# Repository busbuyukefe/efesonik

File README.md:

# efesonik (v2)

A directional soundbar proof-of-concept using cheap 40kHz transducers.

This project can work with the code from [gururise](https://github.com/gururise/directional_speaker) and uses the STM32-bluepill library of [yet-another-average-joe](https://github.com/yet-another-average-joe/Kicad-STM32)

On the [PDF](https://github.com/busbuyukefe/efesonik/blob/main/Parametrik%20Hoparl%C3%B6r.pdf) you can find my notes about the price, working principle and things like layout of the transducers I took while planning/designing the project.

This system has a set of parametric-speaker arranged side-by-side with independent angle control for each one. This allows the system to be focused on more than one targets thus making a more usable. With each section being able to rotate independently it takes less space with the rotating-mechanism than a single speaker with a gimbal.

You can see the code I used in this [gist](https://gist.github.com/busbuyukefe/7ff0d10a8e1e2d5ed5e22a36067409bf) I posted quite a while ago (Which is essentialy the same code from gururise but with a different pinout)

In the amp section of the block diagram you can use anything else to handle the switching. 
The KiCAD drawing has a single sided PCB design but I didn't had the time to check if it is working.

## I sold this project to someone around March of 2021 so I no longer have it.

Video of the first test with the STM32 driver using an old parametric array I built:

Some photos I took during building it:

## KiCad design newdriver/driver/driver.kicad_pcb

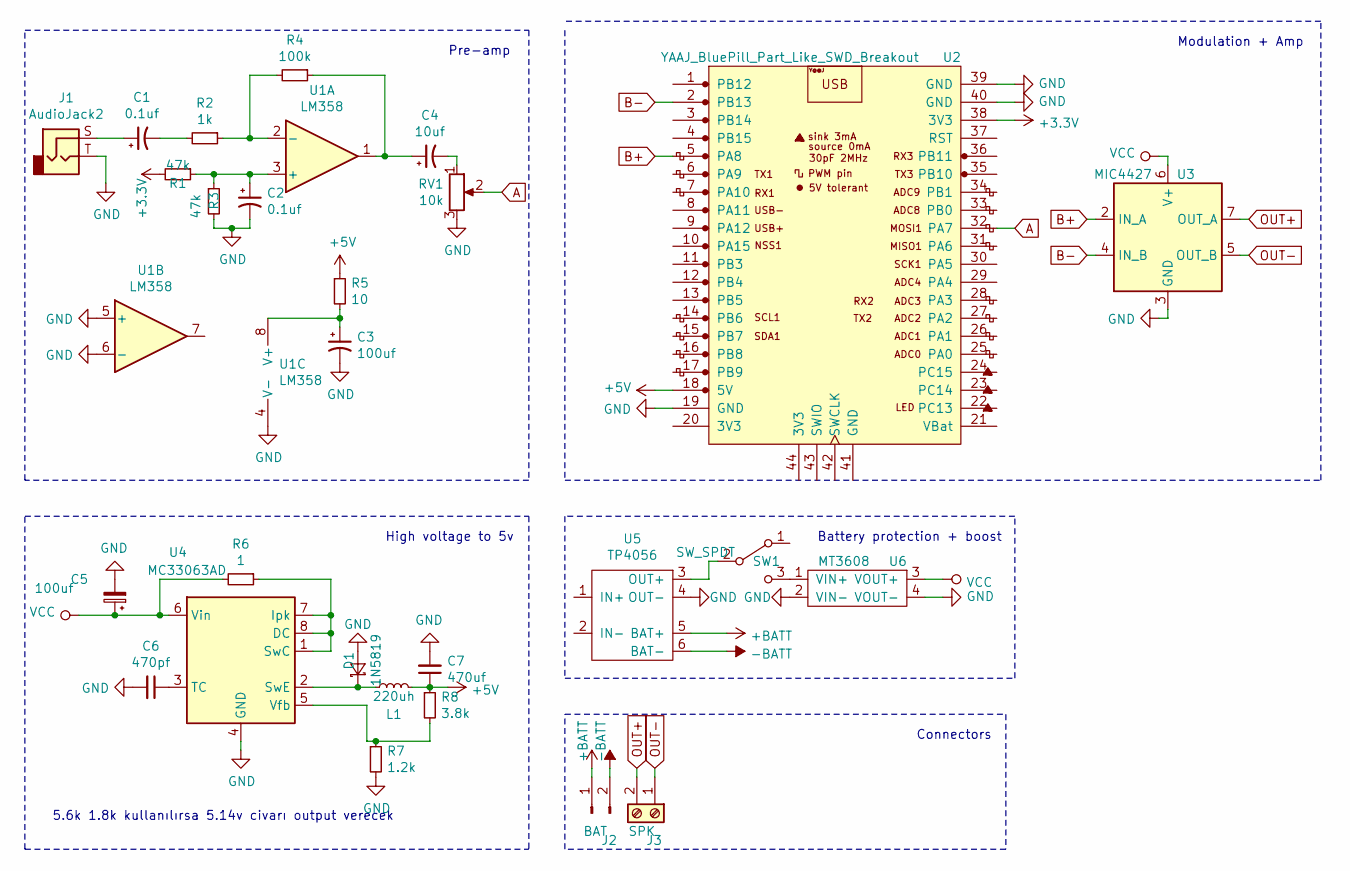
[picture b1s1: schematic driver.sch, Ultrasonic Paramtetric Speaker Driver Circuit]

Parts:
C1, C2: 0.1uf; C_1206_3216Metric
C3, C5: 100uf; C_1206_3216Metric
C4: 10uf; C_1206_3216Metric
C6: 470pf; C_1206_3216Metric
C7: 470uf; C_1206_3216Metric
D1: 1N5819; D_SMA
J1: AudioJack2; PJ-320B
J2: BAT; PinSocket_1x02_P2.54mm_Vertical
J3: SPK; TerminalBlock_bornier-2_P5.08mm
L1: 220uh; L_12x12mm_H4.5mm
R1, R3: 47k; R_1206_3216Metric
R2: 1k; R_1206_3216Metric
R4: 100k; R_1206_3216Metric
R5: 10; R_1206_3216Metric
R6: 1; R_1206_3216Metric
R7: 1.2k; R_1206_3216Metric
R8: 3.8k; R_1206_3216Metric
RV1: 10k; Potentiometer_Bourns_3314G_Vertical
SW1: SW_SPDT; PinSocket_1x03_P2.54mm_Vertical
U1: LM358; SOIC-8_3.9x4.9mm_P1.27mm
U2: YAAJ_BluePill_Part_Like_SWD_Breakout; YAAJ_BluePill_2
U3: MIC4427; SOIC-8_3.9x4.9mm_P1.27mm
U4: MC33063AD; SOIC-8_3.9x4.9mm_P1.27mm
U5: TP4056
U6: MT3608

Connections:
+3V3: R1.2, U2.38 (3V3)
+5V: C7.1, L1.2, R5.1, R8.1, U2.18 (5V)
+BATT: J2.1, U5.5 (BAT+)
-BATT: J2.2, U5.6 (BAT-)
A: RV1.2, U2.32 (PA7)
B+: U2.5 (PA8), U3.2 (IN_A)
B-: U2.2 (PB13), U3.4 (IN_B)
GND: C2.2, C3.2, C5.2, C6.2, C7.2, D1.2 (A), J1.T, R3.2, R7.2, RV1.3, U1.4 (V-), U1.5 (+), U1.6 (-), U2.19 (GND), U2.39 (GND), U2.40 (GND), U3.3 (GND), U4.4 (GND), U5.4 (OUT-), U6.2 (VIN-), U6.4 (VOUT-)
unnamed: C1.1, J1.S
unnamed: C1.2, R2.2
unnamed: C2.1, R1.1, R3.1, U1.3 (+)
unnamed: C3.1, R5.2, U1.8 (V+)
unnamed: C4.1, R4.1, U1.1
unnamed: C4.2, RV1.1
unnamed: C6.1, U4.3 (TC)
unnamed: D1.1 (K), L1.1, U4.2 (SwE)
unnamed: R2.1, R4.2, U1.2 (-)
unnamed: R6.1, U4.1 (SwC), U4.7 (Ipk), U4.8 (DC)
unnamed: R7.1, R8.2, U4.5 (Vfb)
unnamed: SW1.2 (B), U5.3 (OUT+)
unnamed: SW1.3 (C), U6.1 (VIN+)
OUT+: J3.2, U3.7 (OUT_A)
OUT-: J3.1, U3.5 (OUT_B)
VCC: C5.1, R6.2, U3.6 (V+), U4.6 (Vin), U6.3 (VOUT+)

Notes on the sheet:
High voltage to 5v
Pre-amp
Modulation + Amp
Battery protection + boost
Connectors
5.6k 1.8k kullanılırsa 5.14v civarı output verecek

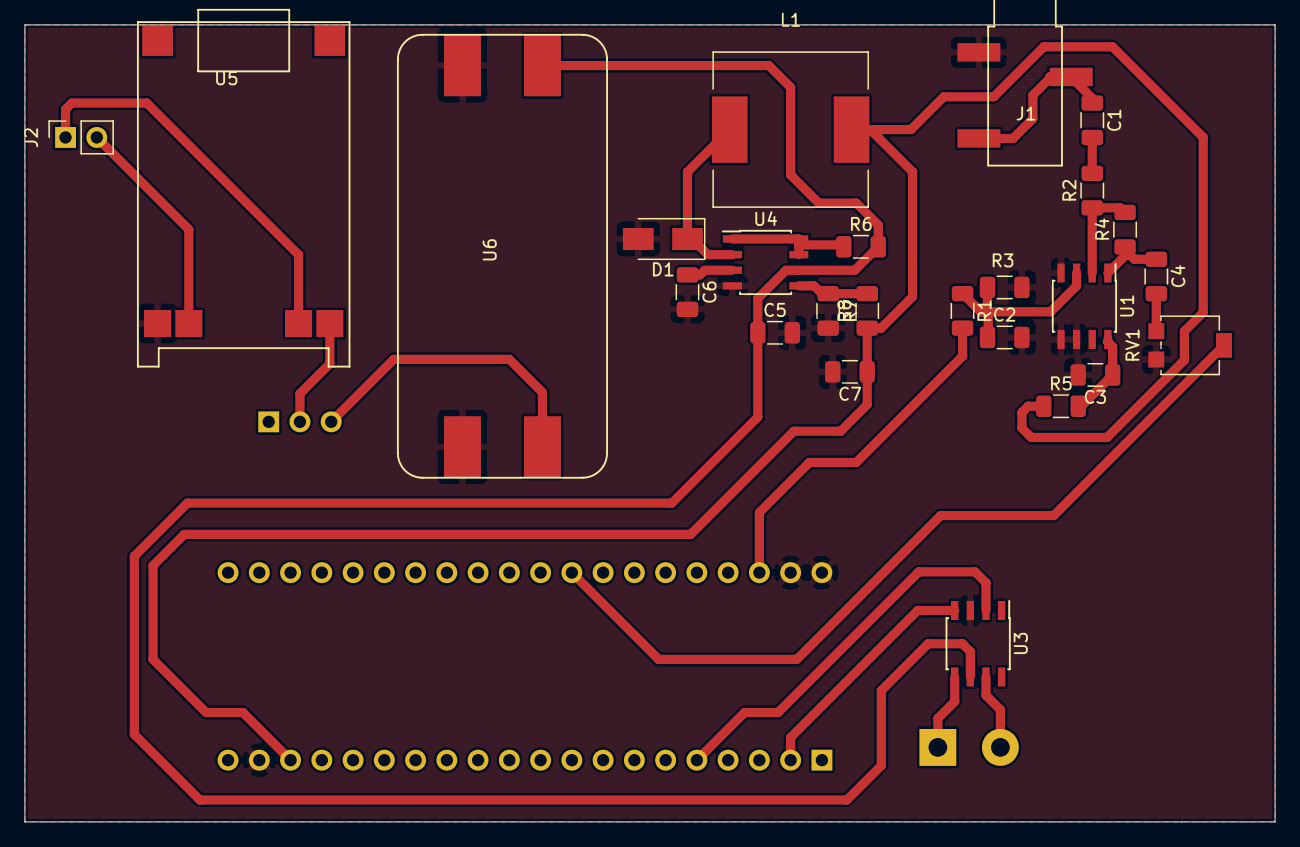
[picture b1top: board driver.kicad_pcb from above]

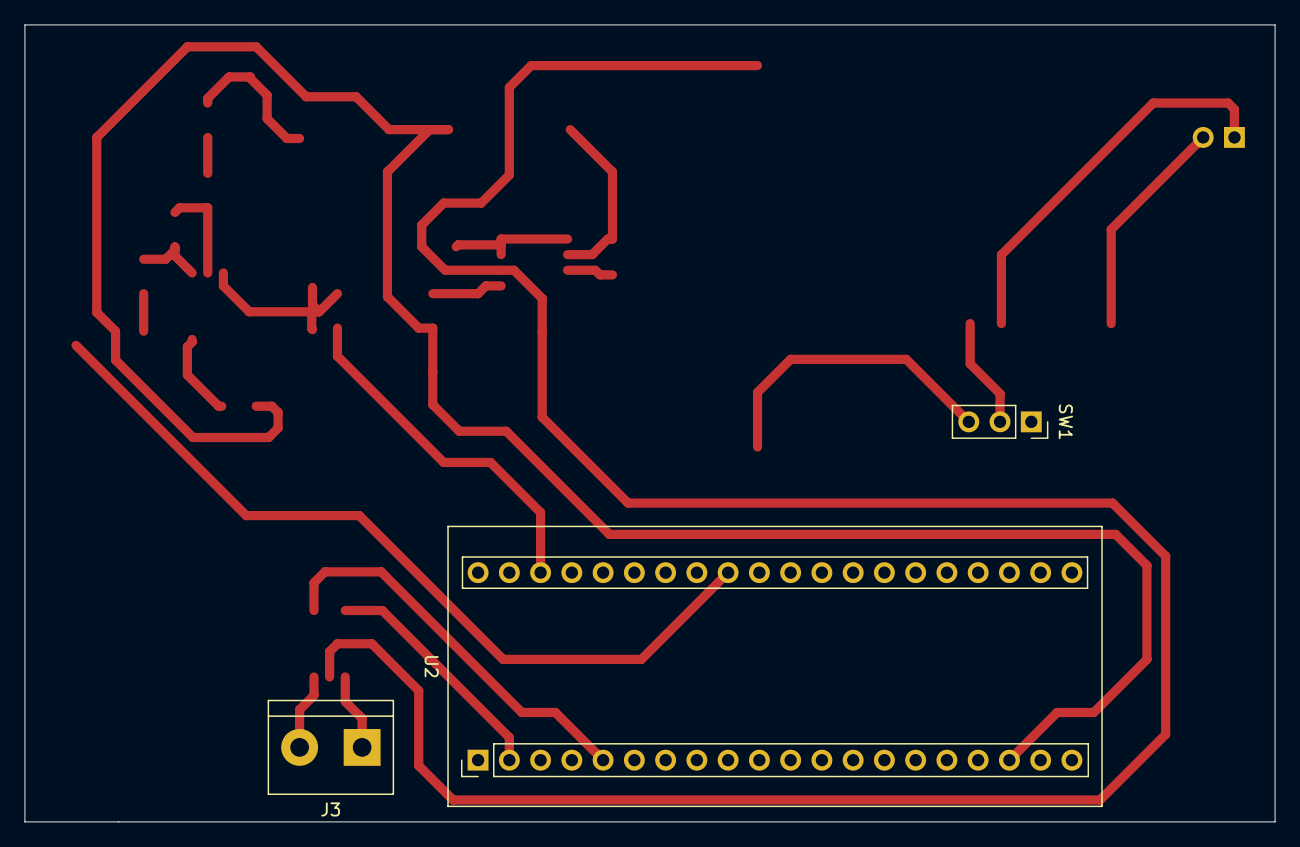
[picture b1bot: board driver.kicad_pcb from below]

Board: 2 copper layers, 101.6 x 64.8 mm, 28 parts (3 on the bottom side), 24 nets.

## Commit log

2021-12-11 First dump of old files
2021-12-11 First set of photos I found from my gallery.
2021-12-11 Added buildlog photos
2021-12-11 Schematics for those don't have KiCAD
2021-12-11 Added schematic to README
2021-12-11 Assembly like preview from FreeCAD
2021-12-11 Updates on the content
